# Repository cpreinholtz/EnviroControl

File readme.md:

# Overview - Enviro Control
This repo contains PCB designs and Arduino firmware for controlling lights and fans via PWM.

Driecotry structure:

cad
doc
firmware
hardware
production
simulation

**PCBs (see detailed descriptions below)**
* SmartPwm_v1, **obsolete**, was an attempt to put multiple pwm outputs onto a esp32 based board.
* HANA, **H**abitation **A**mbiance **N**ano based **A**utomation

## HANA Hardware

### Hardare Overview
The goal of the HANA board is to be a modular PWM controller for either leds or DC fans.  With the latest Arduino nano 33 BLE IOT/SENSE boards it should be possible to cheaply and easily create a wirless notwork of these modules, controllable via an app or master control box.  Additionally the BLE SENSE has fun things like temperature and light sensors which allow for fun closed loop control systems.  The goals are to be relativley cheap, low SWAP, modular, and easily deployable into a 12-14.4v van electrical system.

### Hardare Features
tbd

### Hardware Installation
* Battery GND
* Load -
* Load +
* Battery +

### Hardware Future Considerations
* **User Interface**
* PEC11R / 12R rotary encoder with switch for local control.
* Leds for local display / user interface.
* On off switch for complete power shutoff?, maybe just handle this with a sleep mode at button press?
* Overide switch (2 throw, 1 pole) to connect load return direct to gnd and disconnect from fet, eliminating voltage loss from Vds.

* **Electrical Design Considerations**
* backwards compatability. would it be possible to use old nano, new nano BLE, BLE SENSE, BLE IOT? probably not without a 5v regulator.  seems like 14.4 volts will be OK but the regulator may get too hot and shut down.
* varying pwm frequency on the original nano is found here: https://forum.arduino.cc/t/varying-the-pwm-frequency-for-timer-0-or-timer-2/16679/5. grouping is pins 5+6, 9+10, 11+3 but changing TCRB0 is not reccomended (i.e. not reccomended to change for pins 5+6).  I used pin  9 in my orginal fan design.
* varying pwm freq on the BLE is found here https://forum.arduino.cc/t/changing-pwm-frequency-25khz-4-pin-fan/669549, can be done on any pin.
* 5v reg, probably only needed if backward compatability is needed because i think the new nanos handle 12v
* Over current shutoff? how to detect a fault on the load lines?
* 14.4V max Input voltage sense. volt div or otherwise for a low voltage cutoff to be enabled for battery protection. I have the design for 25K 5K voltage divider, meaning ADC will see 1/6 of power rail, should be 2.4v max
* Do I need a heatsink if I am using a fet driver? perhaps I should add the abilty to install one just in case.
* vertical, or horizintal, or barrel Fets.  Barrel is not enough for the fan, but perhaps LEDS it would work... Horizontal might make sense if only one fet is needed per board. vertical makes sense if mutiple and we can manage heat.

* powering the board: The HTS221 humidity and temperature sensor: Due to self-heating, when the board is powered by USB, the HTS221 becomes unreliable and shows an offset in each reading that changes with the external temperature. To obtain reliable measurements, the board shall be powered by the 3v3 pin, this could be done by cutting the +3V3 solder jumper on the bottom and powering the board through the VIN pin.
* perhaps consider a 3v3 reg in puture designs but in this case I am going to omit this for simplicity.
* led spec'd for i=20mA v = 2.1v... VR = 3.3 - Vled = 1.2V...   r = v/i = 1.2v/ 20mA = 60 ohms, 120 would be 10 mA
* Leds if running direct from 12v max 14.4, Vr = 14.4 - 2.1 = 12.3.  R = 12.3/20e-3 = 615 ohms

* **Mechanical Design Considerations**
* Easy spaced mounting holes and encoder location for use with CNCed, 3d printed, or lazer cut cases
* long shaft encoder for use with a case.
* User freindly Silk screen for easy install.

* **External Connections**
* really only need 4 wired external connections, battery+-, Load+-, although if using n channel fets the load and battery share the + side, (load return is not the same as gnd with N channel fets!).  consider if you want to use ring terminals, screw down clamps, or some other method (solder, spring based, etc).
* daisy chain? I.E. an extra 12v and gnd connector.
* LORA. Add ability to connect or transmit to a LORA module to enable a temperature alarm.
* perhaps add ability to connect to lcd display, fastleds (they now make a truly 12v version), etc.

## HANA Firmware

### Firware Overview
The firware uses Arduino Version 1.8.13.  Firmware is currently a work in progress, I.E. not yet started.

### Firmware Future Considerations
* pwm frequency modifiers for bringing the fan control out of audible ranges.
* Sleep timers for auto shut off at bed time.
* closed loop bang bang contol system for fans. make sure to add hysteresis to avoid oddities.
* logging of temperatures and pwm settings every N minutes.
* dumping of pwm settings and or temp etc every n minutes, or upon request.
* low voltage shutoff.
* temperature allarm, either dump to BLE and or or use LORA module to get a warning to the user

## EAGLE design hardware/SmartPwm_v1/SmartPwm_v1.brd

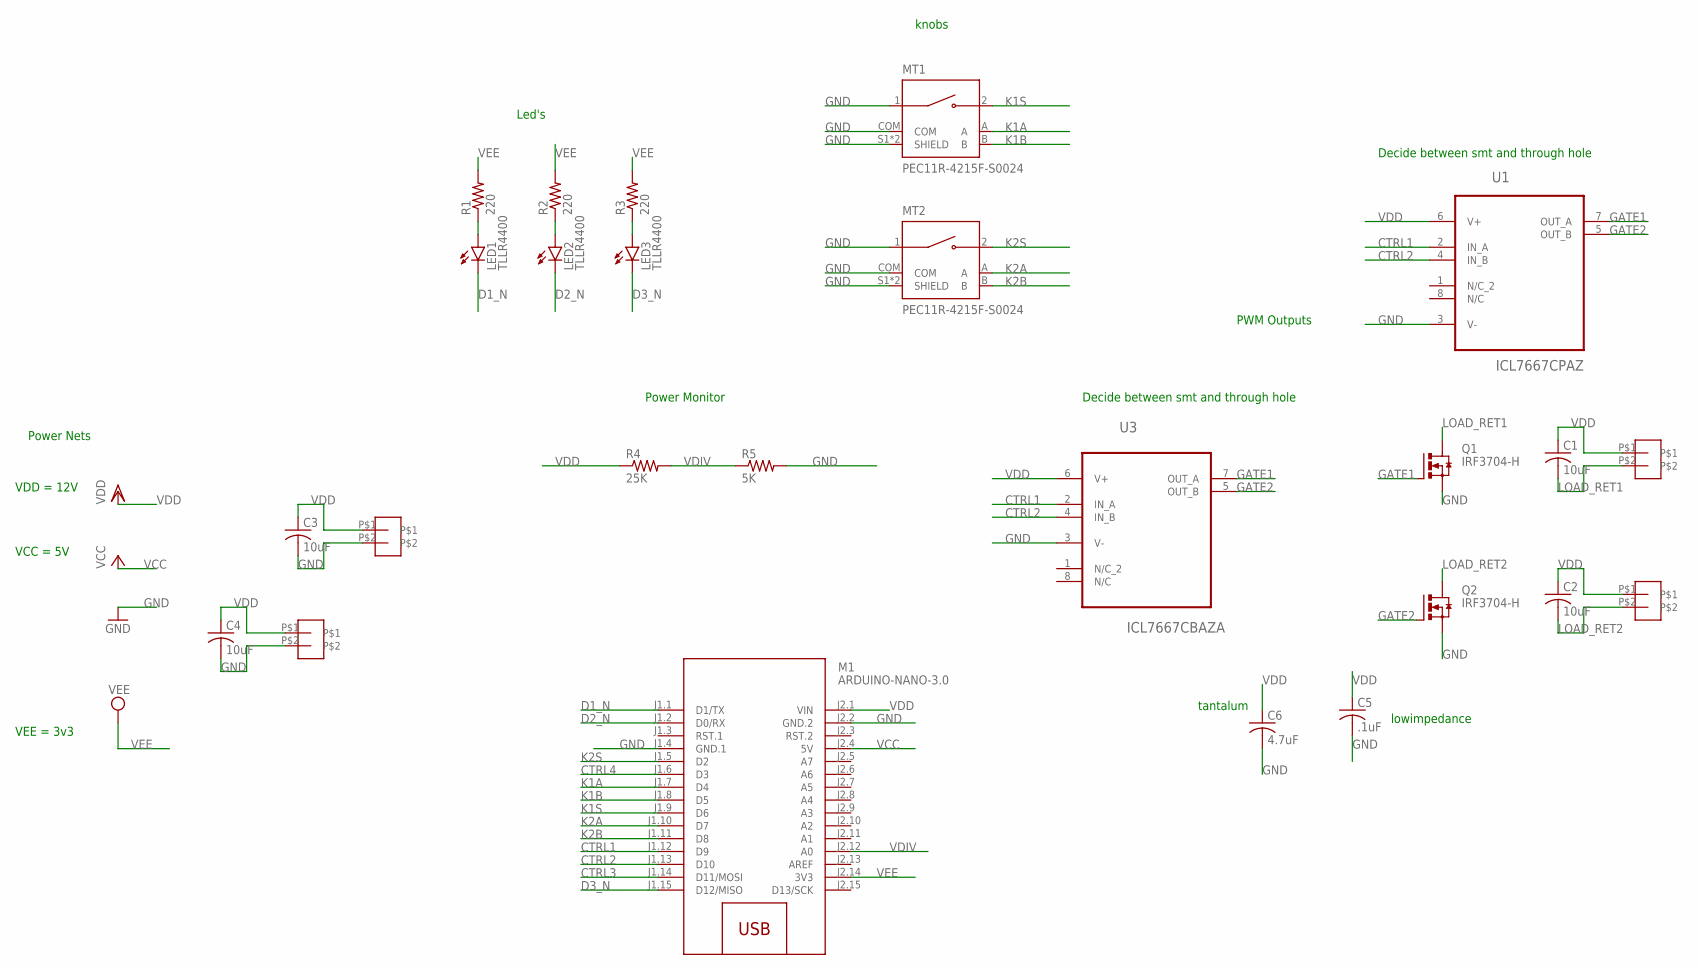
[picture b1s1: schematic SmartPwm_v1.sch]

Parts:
C1, C2, C3, C4: 10uF; C025-024X044
C5: .1uF; C025-024X044
C6: 4.7uF; C025-024X044
LED1, LED2, LED3: TLLR4400; LED3MM
M1: ARDUINO-NANO-3.0
MT1, MT2: PEC11R-4215F-S0024; XDCR_PEC11R-4215F-S0024
Q1, Q2: IRF3704-H; TO220BH
R1, R2, R3: 220; 0207/10
R4: 25K; 0207/10
R5: 5K; 0207/10
U1: ICL7667CPAZ; DIP254P762X533-8
U3: ICL7667CBAZA; SOIC127P600X175-8N
U$1, U$2, U$5, U$8: TB002-500-P02

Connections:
CTRL1: M1.J1.12 (D9), U1.2 (IN_A), U3.2 (IN_A)
CTRL2: M1.J1.13 (D10), U1.4 (IN_B), U3.4 (IN_B)
CTRL3: M1.J1.14 (D11/MOSI)
CTRL4: M1.J1.6 (D3)
D1_N: LED1.K (C), M1.J1.1 (D1/TX)
D2_N: LED2.K (C), M1.J1.2 (D0/RX)
D3_N: LED3.K (C), M1.J1.15 (D12/MISO)
GATE1: Q1.G, U1.7 (OUT_A), U3.7 (OUT_A)
GATE2: Q2.G, U1.5 (OUT_B), U3.5 (OUT_B)
GND: C3.2, C4.2, C5.2, C6.2, M1.J1.4 (GND.1), M1.J2.2 (GND.2), MT1.1, MT1.COM, MT1.S1 (SHIELD), MT1.S2 (SHIELD), MT2.1, MT2.COM, MT2.S1 (SHIELD), MT2.S2 (SHIELD), Q1.S, Q2.S, R5.2, U1.3 (V-), U3.3 (V-), U$5.P$2, U$8.P$2
K1A: M1.J1.7 (D4), MT1.A
K1B: M1.J1.8 (D5), MT1.B
K1S: M1.J1.9 (D6), MT1.2
K2A: M1.J1.10 (D7), MT2.A
K2B: M1.J1.11 (D8), MT2.B
K2S: M1.J1.5 (D2), MT2.2
LOAD_RET1: C1.2, Q1.D, U$1.P$2
LOAD_RET2: C2.2, Q2.D, U$2.P$2
unnamed: LED1.A, R1.1
unnamed: LED2.A, R2.1
unnamed: LED3.A, R3.1
VCC: M1.J2.4 (5V)
VDD: C1.1, C2.1, C3.1, C4.1, C5.1, C6.1, M1.J2.1 (VIN), R4.1, U1.6 (V+), U3.6 (V+), U$1.P$1, U$2.P$1, U$5.P$1, U$8.P$1
VDIV: M1.J2.12 (A0), R4.2, R5.1
VEE: M1.J2.14 (3V3), R1.2, R2.2, R3.2

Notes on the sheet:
Power Nets
VDD = 12V
VCC = 5V
PWM Outputs
knobs
Power Monitor
VEE = 3v3
tantalum
lowimpedance
Led's
Decide between smt and through hole

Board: 2 copper layers, 25 parts (0 on the bottom side), 22 nets, no tracks yet.

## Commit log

2021-08-24 add eagle extensions to gitignore
2021-08-24 add data sheets and start creating schematic
2021-08-24 add esp32 headers to shematic, add 4 control lines for pwm
2021-08-24 Add header for IIC LCD display and add dht11 temp sensor
2021-09-10 add knobs to schematic, rearrange ios, select lcd and add to docs
2021-09-10 add optional grove connector for IIC bus
2021-09-11 swap out components for smt options, research jst 4 pin for leds
2021-09-11 add 3 more led strips, time to start layout!
2021-09-14 remove 1 knob, add 3 individual leds, start component placment
2021-09-28 redo placment for more efficient routing
2021-09-28 rewire gpios, preliminary routing
2021-09-28 did routing, but need to fix ctrl pins, since they were routed to inputs on the pico kit...
2022-03-16 start brainstorming for Nano based pwm module
2022-03-18 continue readme
2022-03-19 begin schematic for nano BLE sense based pwm module
2022-03-19 back to through hole design...

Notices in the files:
parts and their libraries:
diy-modules: Released under the Creative Commons Attribution 4.0 International License: http://creativecommons.org/licenses/by/4.0
